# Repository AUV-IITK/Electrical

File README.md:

# Hyperion-Electrical

The repo contains all the schematics, PCB designs, simulations and other files related to Electrical subsystem of AUV-IITK including both past and current projects. A short description of every subdirectory is provided below in the reverse chronological order.

## actuator_board_v1.0 
The team is set to design and fabricate a single PCB for all the drivers that are needed for the actuators in the vehicle. The board also contains a slightly modified version and custom layout of Arduino Mega 2560's [reference design](https://www.arduino.cc/en/uploads/Main/arduino-mega2560-schematic.pdf?). Other than that, the following components form the crux of the board:

[MC34932](https://www.nxp.com/docs/en/data-sheet/MC34932.pdf) Dual H-Bridge Motor Driver to drive [BTD150 Thrusters](http://ocean-innovations.net/OceanInnovationsNEW/SeaBotix/BTD150_Data_Sheet.pdf) from SeaBotix

[Basic ESC R3](http://docs.bluerobotics.com/bescr3/) ESC from BlueRobotics to drive [T200 Thrusters](https://www.bluerobotics.com/store/thrusters/t200-thruster/) also from BlueRobotics

[DRV102](http://www.ti.com/product/DRV102) PWM Solenoid driver from Texas Instruments to control solenoid operated valves

## actuator_board_v0.1
This board is a prototype board intended to test the [MC34932](https://www.nxp.com/docs/en/data-sheet/MC34932.pdf) motor drivers and [Atmega2560](http://ww1.microchip.com/downloads/en/DeviceDoc/Atmel-2549-8-bit-AVR-Microcontroller-ATmega640-1280-1281-2560-2561_datasheet.pdf) circuit independently and observe their individual behavior before integrating them into v1.0 board. The board was fabricated and tested and it worked successfully. The team is moved onto designing the v1.0 board.

## BMSv2
This board is a concept-design of a Battery Management System to control, monitor and protect the Lithium Polymer batteries used in the vehicle. This board has not been fabricated due to technical difficulties we faced while testing the ICs. The following components are used in the board:

[Atxmega128A1U](http://ww1.microchip.com/downloads/en/DeviceDoc/Atmel-8385-8-and-16-bit-AVR-Microcontroller-ATxmega64A1U-ATxmega128A1U_datasheet.pdf) microcontroller as the brain of the board

[BQ76930](http://www.ti.com/lit/ds/symlink/bq76920.pdf) and [BQ78350-R1](https://www.ti.com/lit/ds/symlink/bq78350-r1.pdf?HQS=TI-null-null-sf-df-ds-null-wwe) battery management ICs from Texas Instruments

[TPS54531](http://www.ti.com/lit/ds/symlink/tps54531.pdf) Step Down DC-DC converters to create two voltage rails at 3.3V (to power the Atxmega chip) and 15V (To power an [Intel NUC](https://www.intel.in/content/www/in/en/products/boards-kits/nuc/kits/nuc5i7ryh.html) which is the main on-board computer in the vehicle). The board also provides an unregulated rail to power the [BTD150 Thrusters](http://ocean-innovations.net/OceanInnovationsNEW/SeaBotix/BTD150_Data_Sheet.pdf)

[ACS725](https://www.allegromicro.com/en/Products/Current-Sensor-ICs/Zero-To-Fifty-Amp-Integrated-Conductor-Sensor-ICs/ACS725.aspx) Current Sensors to monitor the current in each of the three rails

## BMS
This is a rudimentary battery management board that was created to act as a back-plane to connect multiple third-party modules. The board has been fabricated and tested and it worked succesfully. The board, however, didn't make it into the vehicle due to its large size.

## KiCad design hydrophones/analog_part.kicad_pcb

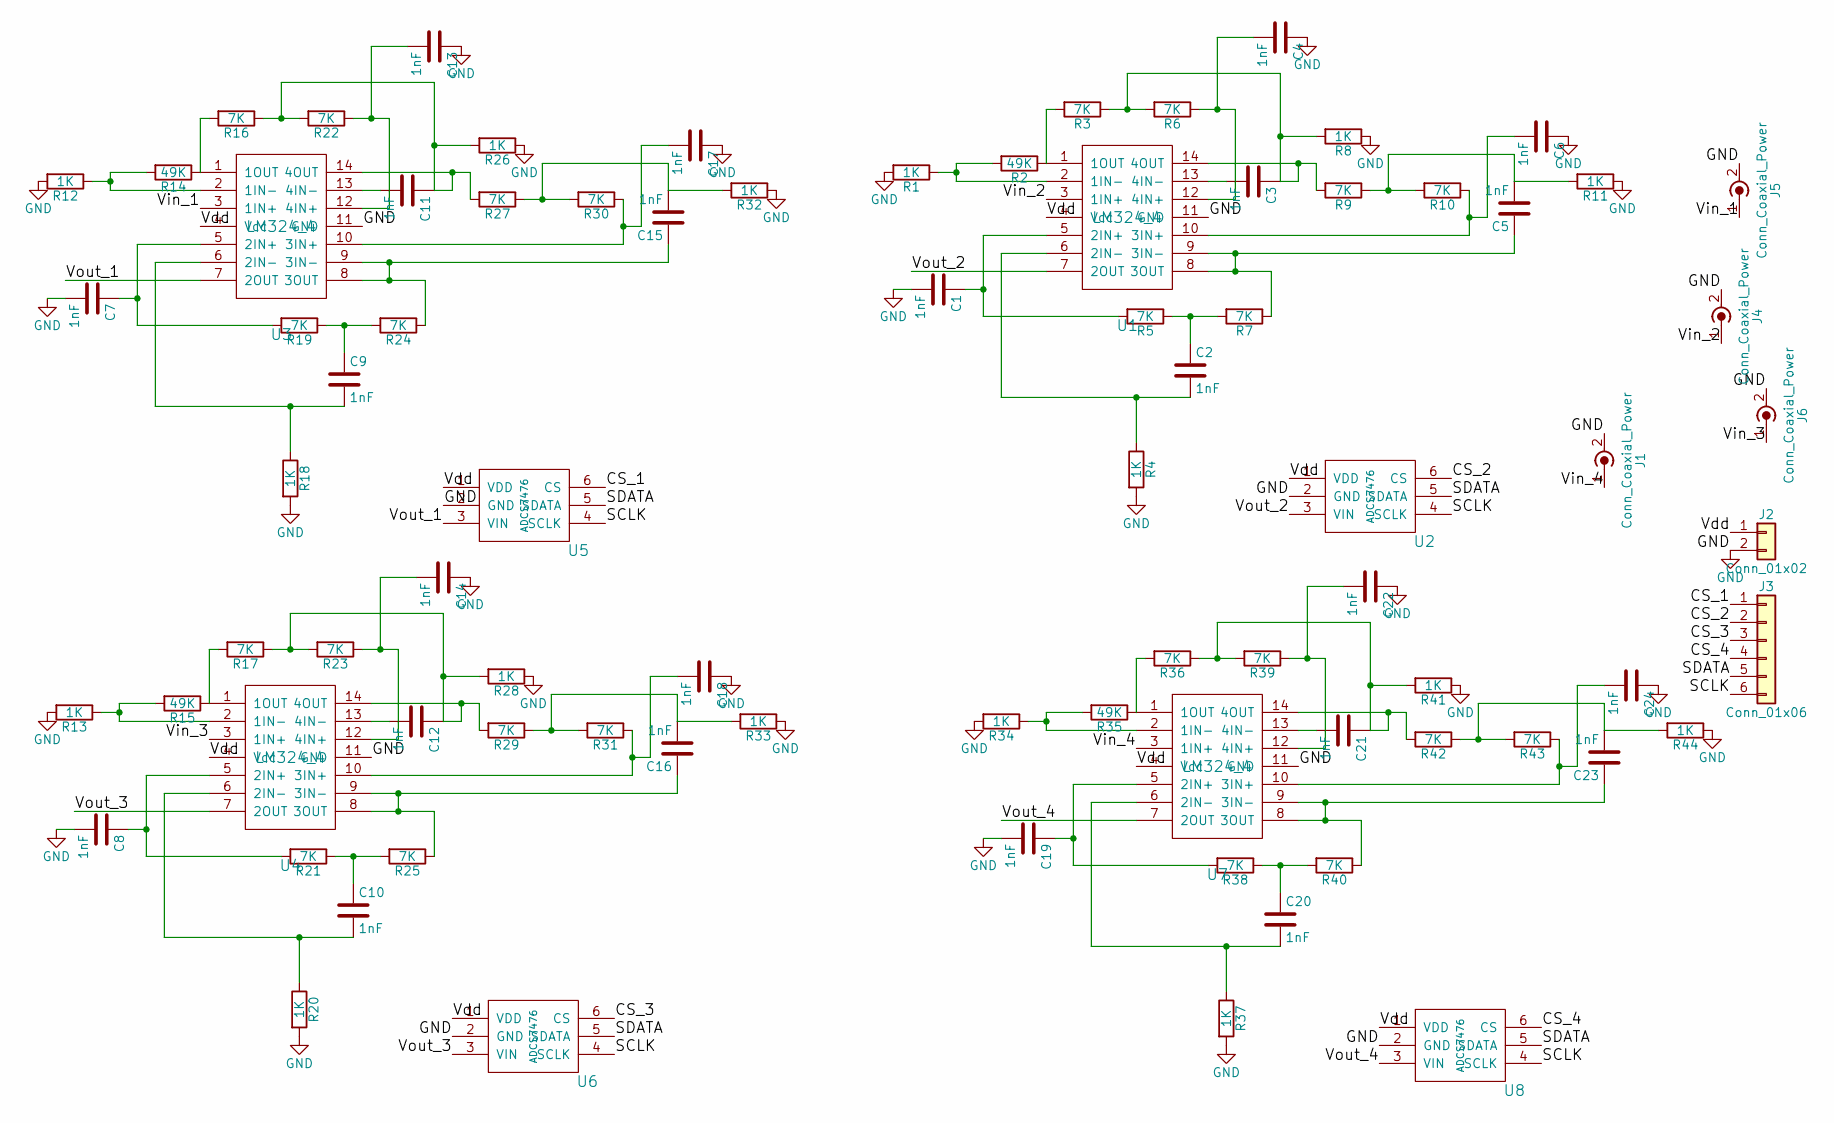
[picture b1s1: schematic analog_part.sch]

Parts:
C1, C2, C3, C4, C5, C6, C7, C8, C9, C10, C11, C12, C13, C14, C15, C16, C17, C18, C19, C20, C21, C22, C23, C24: 1nF; C_1206_HandSoldering
J1, J4, J5, J6: Conn_Coaxial_Power; bnc-ci
J2: Conn_01x02; Pin_Header_Angled_1x02_Pitch2.54mm
J3: Conn_01x06; Pin_Header_Angled_1x06_Pitch2.54mm
R1, R4, R8, R11, R12, R13, R18, R20, R26, R28, R32, R33, R34, R37, R41, R44: 1K; R_1206_HandSoldering
R2, R14, R15, R35: 49K; R_1206_HandSoldering
R3, R5, R6, R7, R9, R10, R16, R17, R19, R21, R22, R23, R24, R25, R27, R29, R30, R31, R36, R38, R39, R40, R42, R43: 7K; R_1206_HandSoldering
U1, U3, U4, U7: LM324_4; TSSOP-14_4.4x5mm_Pitch0.65mm
U2, U5, U6, U8: ADCS7476; SOT-23-6_Handsoldering

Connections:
/CS_1: J3.1, U5.6 (CS)
/CS_2: J3.2, U2.6 (CS)
/CS_3: J3.3, U6.6 (CS)
/CS_4: J3.4, U8.6 (CS)
/SCLK: J3.6, U2.4 (SCLK), U5.4 (SCLK), U6.4 (SCLK), U8.4 (SCLK)
/SDATA: J3.5, U2.5 (SDATA), U5.5 (SDATA), U6.5 (SDATA), U8.5 (SDATA)
/Vdd: J2.1, U1.4 (Vcc), U2.1 (VDD), U3.4 (Vcc), U4.4 (Vcc), U5.1 (VDD), U6.1 (VDD), U7.4 (Vcc), U8.1 (VDD)
/Vin_1: J5.1 (In), U3.3 (1IN+)
/Vin_2: J4.1 (In), U1.3 (1IN+)
/Vin_3: J6.1 (In), U4.3 (1IN+)
/Vin_4: J1.1 (In), U7.3 (1IN+)
/Vout_1: U3.7 (2OUT), U5.3 (VIN)
/Vout_2: U1.7 (2OUT), U2.3 (VIN)
/Vout_3: U4.7 (2OUT), U6.3 (VIN)
/Vout_4: U7.7 (2OUT), U8.3 (VIN)
GND: C1.2, C4.1, C6.1, C7.2, C8.2, C13.1, C14.1, C17.1, C18.1, C19.2, C22.1, C24.1, J1.2 (Ext), J2.2, J4.2 (Ext), J5.2 (Ext), J6.2 (Ext), R1.2, R4.2, R8.1, R11.1, R12.2, R13.2, R18.2, R20.2, R26.1, R28.1, R32.1, R33.1, R34.2, R37.2, R41.1, R44.1, U1.11 (GND), U2.2 (GND), U3.11 (GND), U4.11 (GND), U5.2 (GND), U6.2 (GND), U7.11 (GND), U8.2 (GND)
unnamed: C1.1, R5.2, U1.5 (2IN+)
unnamed: C2.1, R5.1, R7.2
unnamed: C2.2, R4.1, U1.6 (2IN-)
unnamed: C3.1, R3.1, R6.2, R8.2, R9.2, U1.14 (4OUT)
unnamed: C3.2, U1.13 (4IN-)
unnamed: C4.2, R6.1, U1.12 (4IN+)
unnamed: C5.1, R7.1, U1.8 (3OUT), U1.9 (3IN-)
unnamed: C5.2, R9.1, R10.2, R11.2
unnamed: C6.2, R10.1, U1.10 (3IN+)
unnamed: C7.1, R19.2, U3.5 (2IN+)
unnamed: C8.1, R21.2, U4.5 (2IN+)
unnamed: C9.1, R19.1, R24.2
unnamed: C9.2, R18.1, U3.6 (2IN-)
unnamed: C10.1, R21.1, R25.2
unnamed: C10.2, R20.1, U4.6 (2IN-)
unnamed: C11.1, R16.1, R22.2, R26.2, R27.2, U3.14 (4OUT)
unnamed: C11.2, U3.13 (4IN-)
unnamed: C12.1, R17.1, R23.2, R28.2, R29.2, U4.14 (4OUT)
unnamed: C12.2, U4.13 (4IN-)
unnamed: C13.2, R22.1, U3.12 (4IN+)
unnamed: C14.2, R23.1, U4.12 (4IN+)
unnamed: C15.1, R24.1, U3.8 (3OUT), U3.9 (3IN-)
unnamed: C15.2, R27.1, R30.2, R32.2
unnamed: C16.1, R25.1, U4.8 (3OUT), U4.9 (3IN-)
unnamed: C16.2, R29.1, R31.2, R33.2
unnamed: C17.2, R30.1, U3.10 (3IN+)
unnamed: C18.2, R31.1, U4.10 (3IN+)
unnamed: C19.1, R38.2, U7.5 (2IN+)
unnamed: C20.1, R38.1, R40.2
unnamed: C20.2, R37.1, U7.6 (2IN-)
unnamed: C21.1, R36.1, R39.2, R41.2, R42.2, U7.14 (4OUT)
unnamed: C21.2, U7.13 (4IN-)
unnamed: C22.2, R39.1, U7.12 (4IN+)
unnamed: C23.1, R40.1, U7.8 (3OUT), U7.9 (3IN-)
unnamed: C23.2, R42.1, R43.2, R44.2
unnamed: C24.2, R43.1, U7.10 (3IN+)
unnamed: R1.1, R2.2, U1.2 (1IN-)
unnamed: R2.1, R3.2, U1.1 (1OUT)
unnamed: R12.1, R14.2, U3.2 (1IN-)
unnamed: R13.1, R15.2, U4.2 (1IN-)
unnamed: R14.1, R16.2, U3.1 (1OUT)
unnamed: R15.1, R17.2, U4.1 (1OUT)
unnamed: R34.1, R35.2, U7.2 (1IN-)
unnamed: R35.1, R36.2, U7.1 (1OUT)

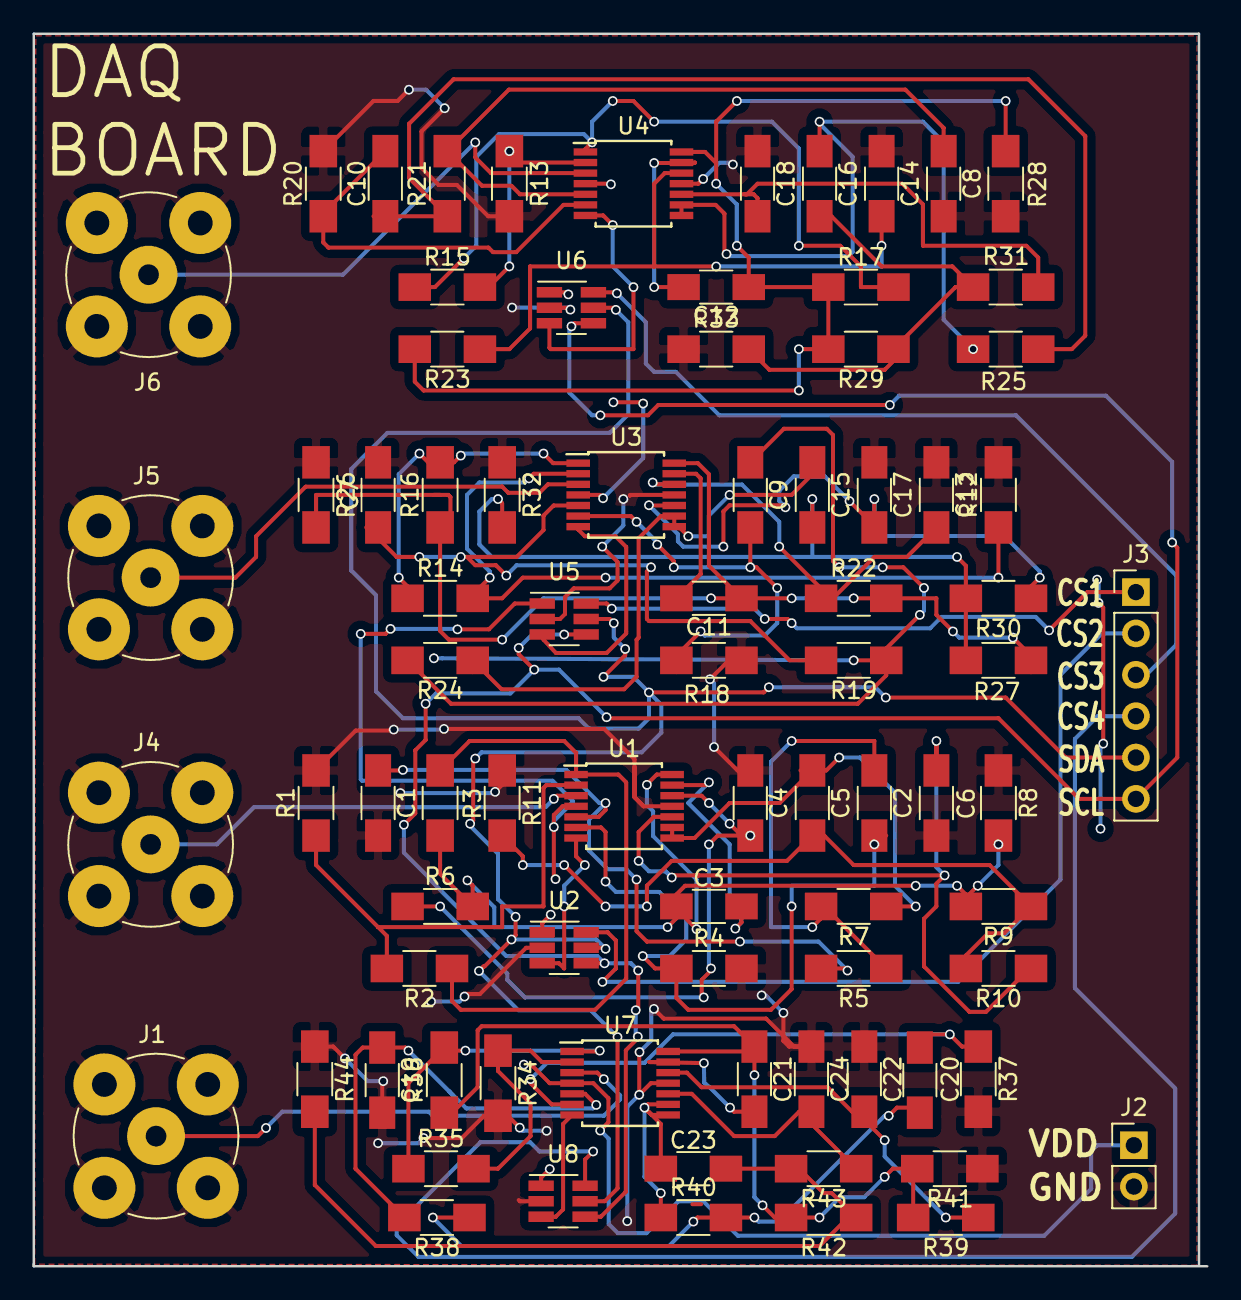
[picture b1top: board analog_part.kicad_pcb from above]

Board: 2 copper layers, 72.1 x 75.7 mm, 82 parts (0 on the bottom side), 60 nets.

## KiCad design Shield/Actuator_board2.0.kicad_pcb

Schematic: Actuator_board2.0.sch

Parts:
J1: Conn_01x05_Male; Pin_Header_Straight_1x05_Pitch2.54mm
J2, J3: Conn_01x13_Female; Socket_Strip_Straight_1x13_Pitch2.54mm
J4, J5, J8, J9, J12: Conn_01x04_Male; Pin_Header_Straight_1x04_Pitch2.54mm
J6: Conn_01x08_Male; Pin_Header_Straight_1x08_Pitch2.54mm
J7: Conn_01x07_Male; Pin_Header_Straight_1x07_Pitch2.54mm
J10, J11: Conn_01x02_Male; Pin_Header_Straight_1x02_Pitch2.54mm
XA1: Arduino_Mega2560_Shield

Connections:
/3.3V: J1.5, J11.1, J11.2, XA1.3V3 (3.3V)
/5V: J1.3, J4.1, J4.2, J4.3, J4.4, XA1.5V1 (5V)
/ANA1: J12.1, XA1.A4
/ANA2: J12.2, XA1.A5
/ANA3: J12.3, XA1.A6
/ANA4: J12.4, XA1.A7
/CS-1: J2.3, XA1.A0
/CS-2: J2.10, XA1.A1
/CS-3: J3.3, XA1.A2
/CS-4: J3.10, XA1.A3
/DIG1: J8.1, XA1.D40
/DIG2: J8.2, XA1.D41
/DIG3: J8.3, XA1.D42
/DIG4: J8.4, XA1.D43
/DIRA-1: J2.5, XA1.D22
/DIRA-2: J2.12, XA1.D24
/DIRA-3: J3.5, XA1.D26
/DIRA-4: J3.12, XA1.D28
/DIRB-1: J2.6, XA1.D23
/DIRB-2: J2.13, XA1.D25
/DIRB-3: J3.6, XA1.D27
/DIRB-4: J3.13, XA1.D29
/GND: J1.4, J2.1, J2.8, J3.1, J3.8, J5.1, J5.2, J5.3, J5.4, J6.2, J6.4, J6.6, J6.8, J7.7, XA1.GND1 (GND)
/PW1: J9.1, XA1.D6
/PW2: J9.2, XA1.D7
/PW3: J9.3, XA1.D8
/PW4: J9.4, XA1.D11
/PWM-1: J2.4, XA1.D2 (D2_INT0)
/PWM-2: J2.11, XA1.D3 (D3_INT1)
/PWM-3: J3.4, XA1.D4
/PWM-4: J3.11, XA1.D5
/S1: J7.1, XA1.D34
/S2: J7.2, XA1.D35
/S3: J7.3, XA1.D36
/S4: J7.4, XA1.D37
/S5: J7.5, XA1.D38
/S6: J7.6, XA1.D39
/SCL: J1.1, XA1.SCL
/SCL1: J10.2, XA1.D21 (D21_SCL)
/SDA: J1.2, XA1.SDA
/SDA1: J10.1, XA1.D20 (D20_SDA)
/T-5: J6.1, XA1.D30
/T-6: J6.3, XA1.D31
/T-7: J6.5, XA1.D32
/T-8: J6.7, XA1.D33

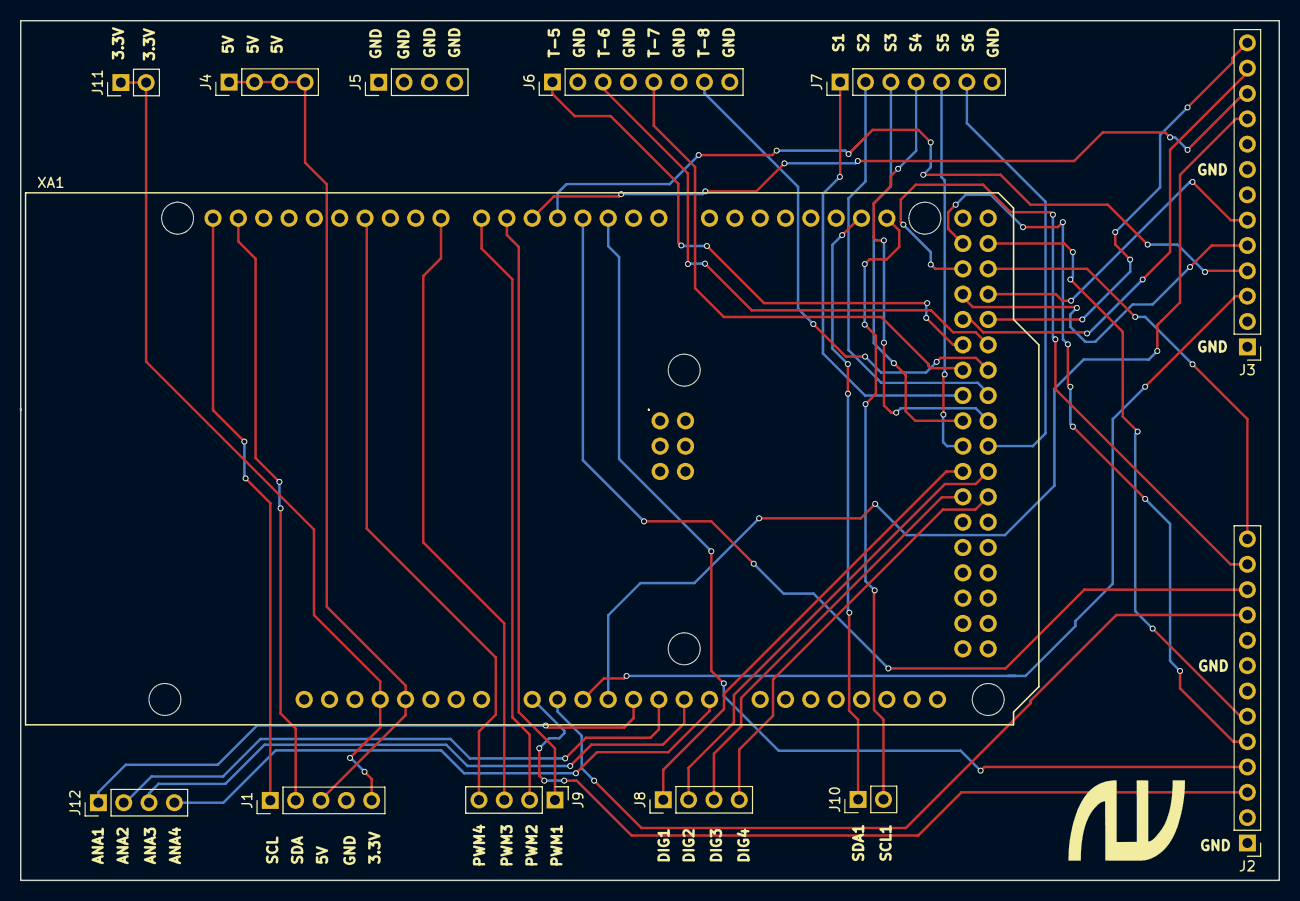
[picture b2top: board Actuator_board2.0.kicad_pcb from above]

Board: 2 copper layers, 126.2 x 86.2 mm, 13 parts (0 on the bottom side), 45 nets.

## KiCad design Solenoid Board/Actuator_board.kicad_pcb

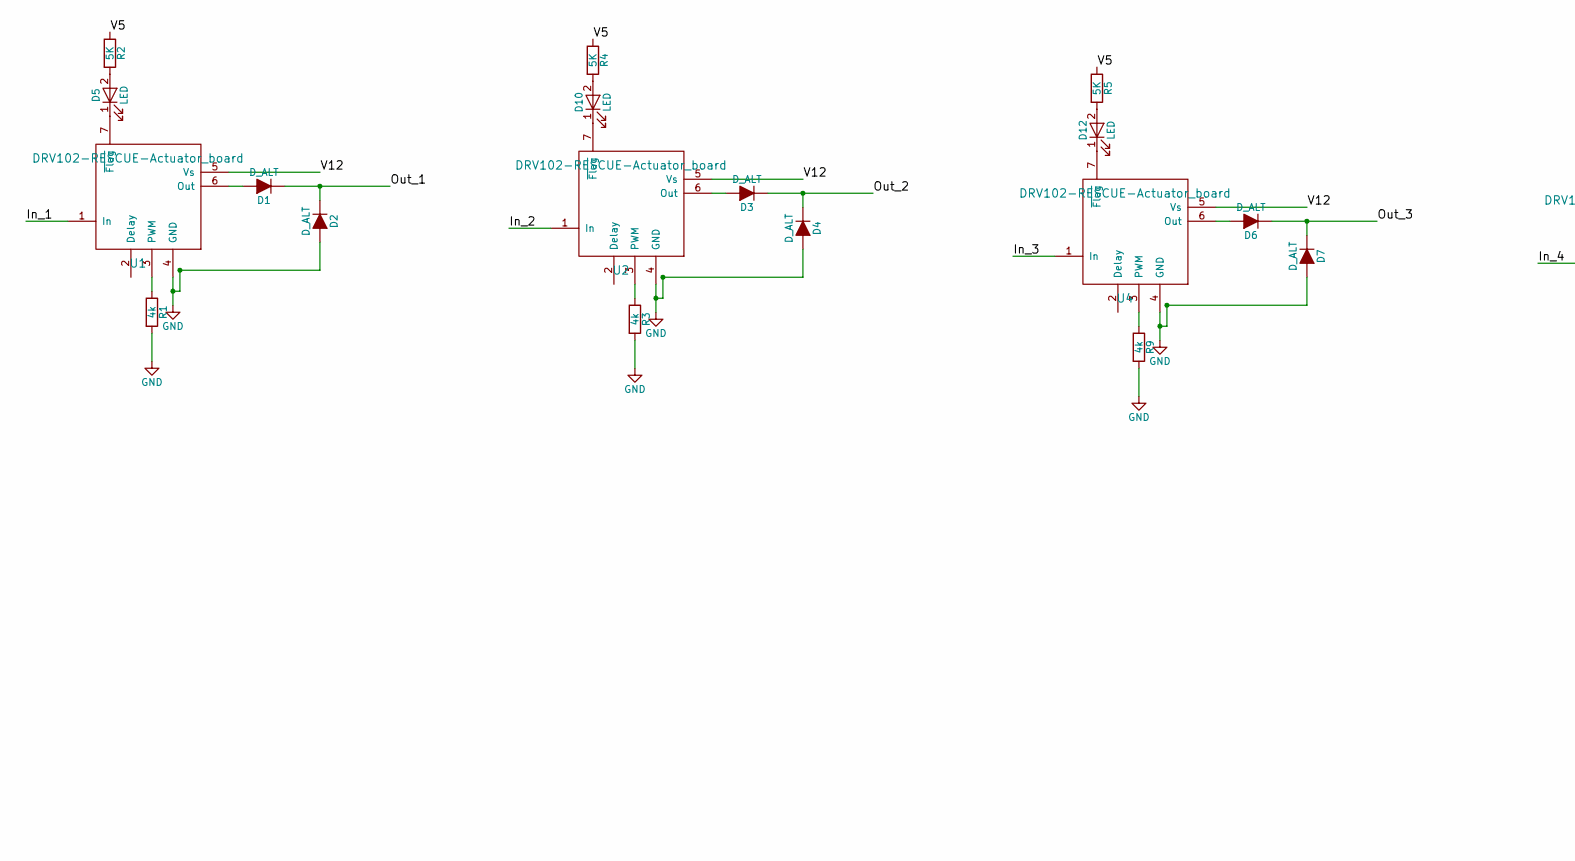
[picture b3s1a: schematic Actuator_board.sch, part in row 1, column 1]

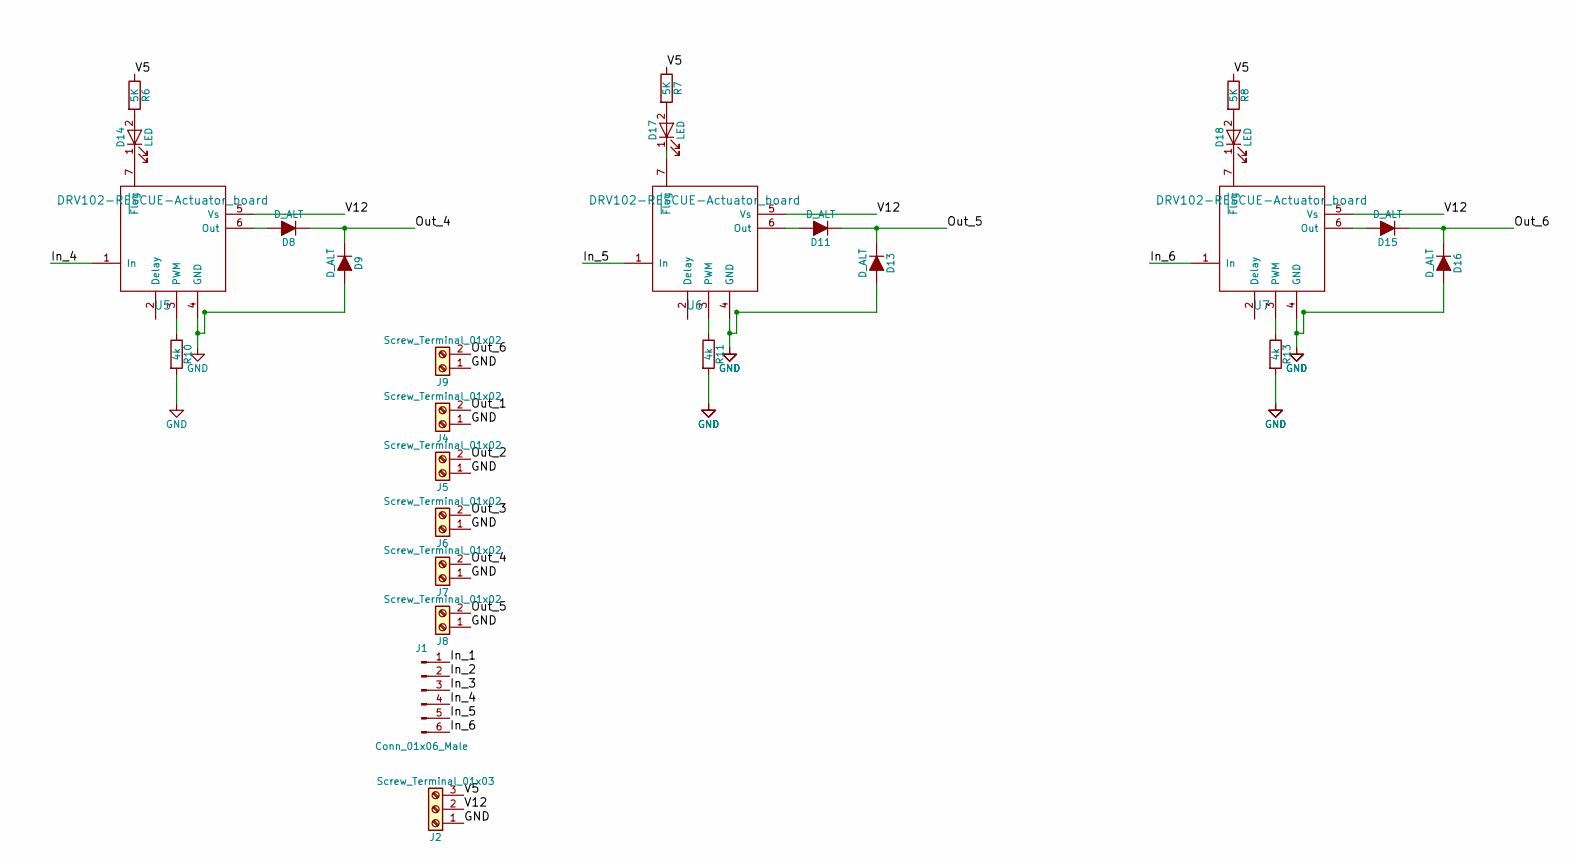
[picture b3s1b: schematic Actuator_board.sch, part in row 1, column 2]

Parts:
D1, D2, D3, D4, D6, D7, D8, D9, D11, D13, D15, D16: D_ALT; DO-214AB
D5: LED; LED_D2.0mm_W4.8mm_H2.5mm_FlatTop
D10, D12, D14, D17, D18: LED; LED_D3.0mm
J1: Conn_01x06_Male; Pin_Header_Straight_1x06_Pitch2.54mm
J2: Screw_Terminal_01x03; TerminalBlock_bornier-3_P5.08mm
J4, J5, J6, J7, J8, J9: Screw_Terminal_01x02; TerminalBlock_bornier-2_P5.08mm
R1, R3, R9, R10, R11, R13: 4k; R_1206
R2, R4, R5, R6, R7, R8: 5K; R_1206
U1, U2, U4, U5, U6, U7: DRV102-RESCUE-Actuator_board; TO-263-7_TabPin4

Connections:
/In_1: J1.1, U1.1 (In)
/In_2: J1.2, U2.1 (In)
/In_3: J1.3, U4.1 (In)
/In_4: J1.4, U5.1 (In)
/In_5: J1.5, U6.1 (In)
/In_6: J1.6, U7.1 (In)
/Out_1: D1.1 (K), D2.1 (K), J4.2
/Out_2: D3.1 (K), D4.1 (K), J5.2
/Out_3: D6.1 (K), D7.1 (K), J6.2
/Out_4: D8.1 (K), D9.1 (K), J7.2
/Out_5: D11.1 (K), D13.1 (K), J8.2
/Out_6: D15.1 (K), D16.1 (K), J9.2
/V5: J2.3, R2.1, R4.1, R5.1, R6.1, R7.1, R8.1
/V12: J2.2, U1.5 (Vs), U2.5 (Vs), U4.5 (Vs), U5.5 (Vs), U6.5 (Vs), U7.5 (Vs)
GND: D2.2 (A), D4.2 (A), D7.2 (A), D9.2 (A), D13.2 (A), D16.2 (A), J2.1, J4.1, J5.1, J6.1, J7.1, J8.1, J9.1, R1.2, R3.2, R9.2, R10.2, R11.2, R13.2, U1.4 (GND), U2.4 (GND), U4.4 (GND), U5.4 (GND), U6.4 (GND), U7.4 (GND)
unnamed: D1.2 (A), U1.6 (Out)
unnamed: D3.2 (A), U2.6 (Out)
unnamed: D5.1 (K), U1.7 (~Flag)
unnamed: D5.2 (A), R2.2
unnamed: D6.2 (A), U4.6 (Out)
unnamed: D8.2 (A), U5.6 (Out)
unnamed: D10.1 (K), U2.7 (~Flag)
unnamed: D10.2 (A), R4.2
unnamed: D11.2 (A), U6.6 (Out)
unnamed: D12.1 (K), U4.7 (~Flag)
unnamed: D12.2 (A), R5.2
unnamed: D14.1 (K), U5.7 (~Flag)
unnamed: D14.2 (A), R6.2
unnamed: D15.2 (A), U7.6 (Out)
unnamed: D17.1 (K), U6.7 (~Flag)
unnamed: D17.2 (A), R7.2
unnamed: D18.1 (K), U7.7 (~Flag)
unnamed: D18.2 (A), R8.2
unnamed: R1.1, U1.3 (PWM)
unnamed: R3.1, U2.3 (PWM)
unnamed: R9.1, U4.3 (PWM)
unnamed: R10.1, U5.3 (PWM)
unnamed: R11.1, U6.3 (PWM)
unnamed: R13.1, U7.3 (PWM)

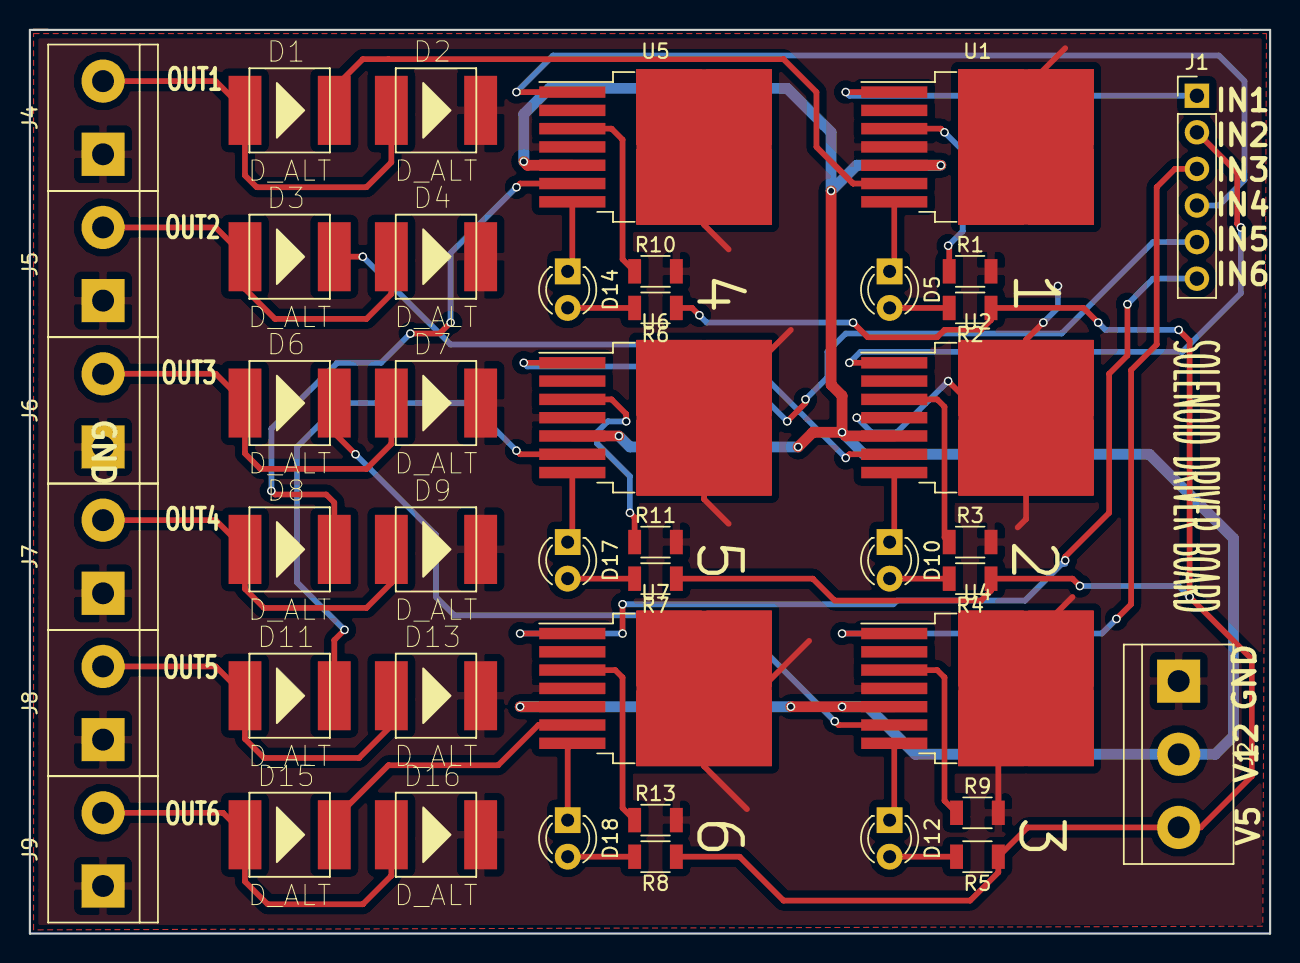
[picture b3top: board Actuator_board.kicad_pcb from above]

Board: 2 copper layers, 86.1 x 62.7 mm, 44 parts (0 on the bottom side), 39 nets.

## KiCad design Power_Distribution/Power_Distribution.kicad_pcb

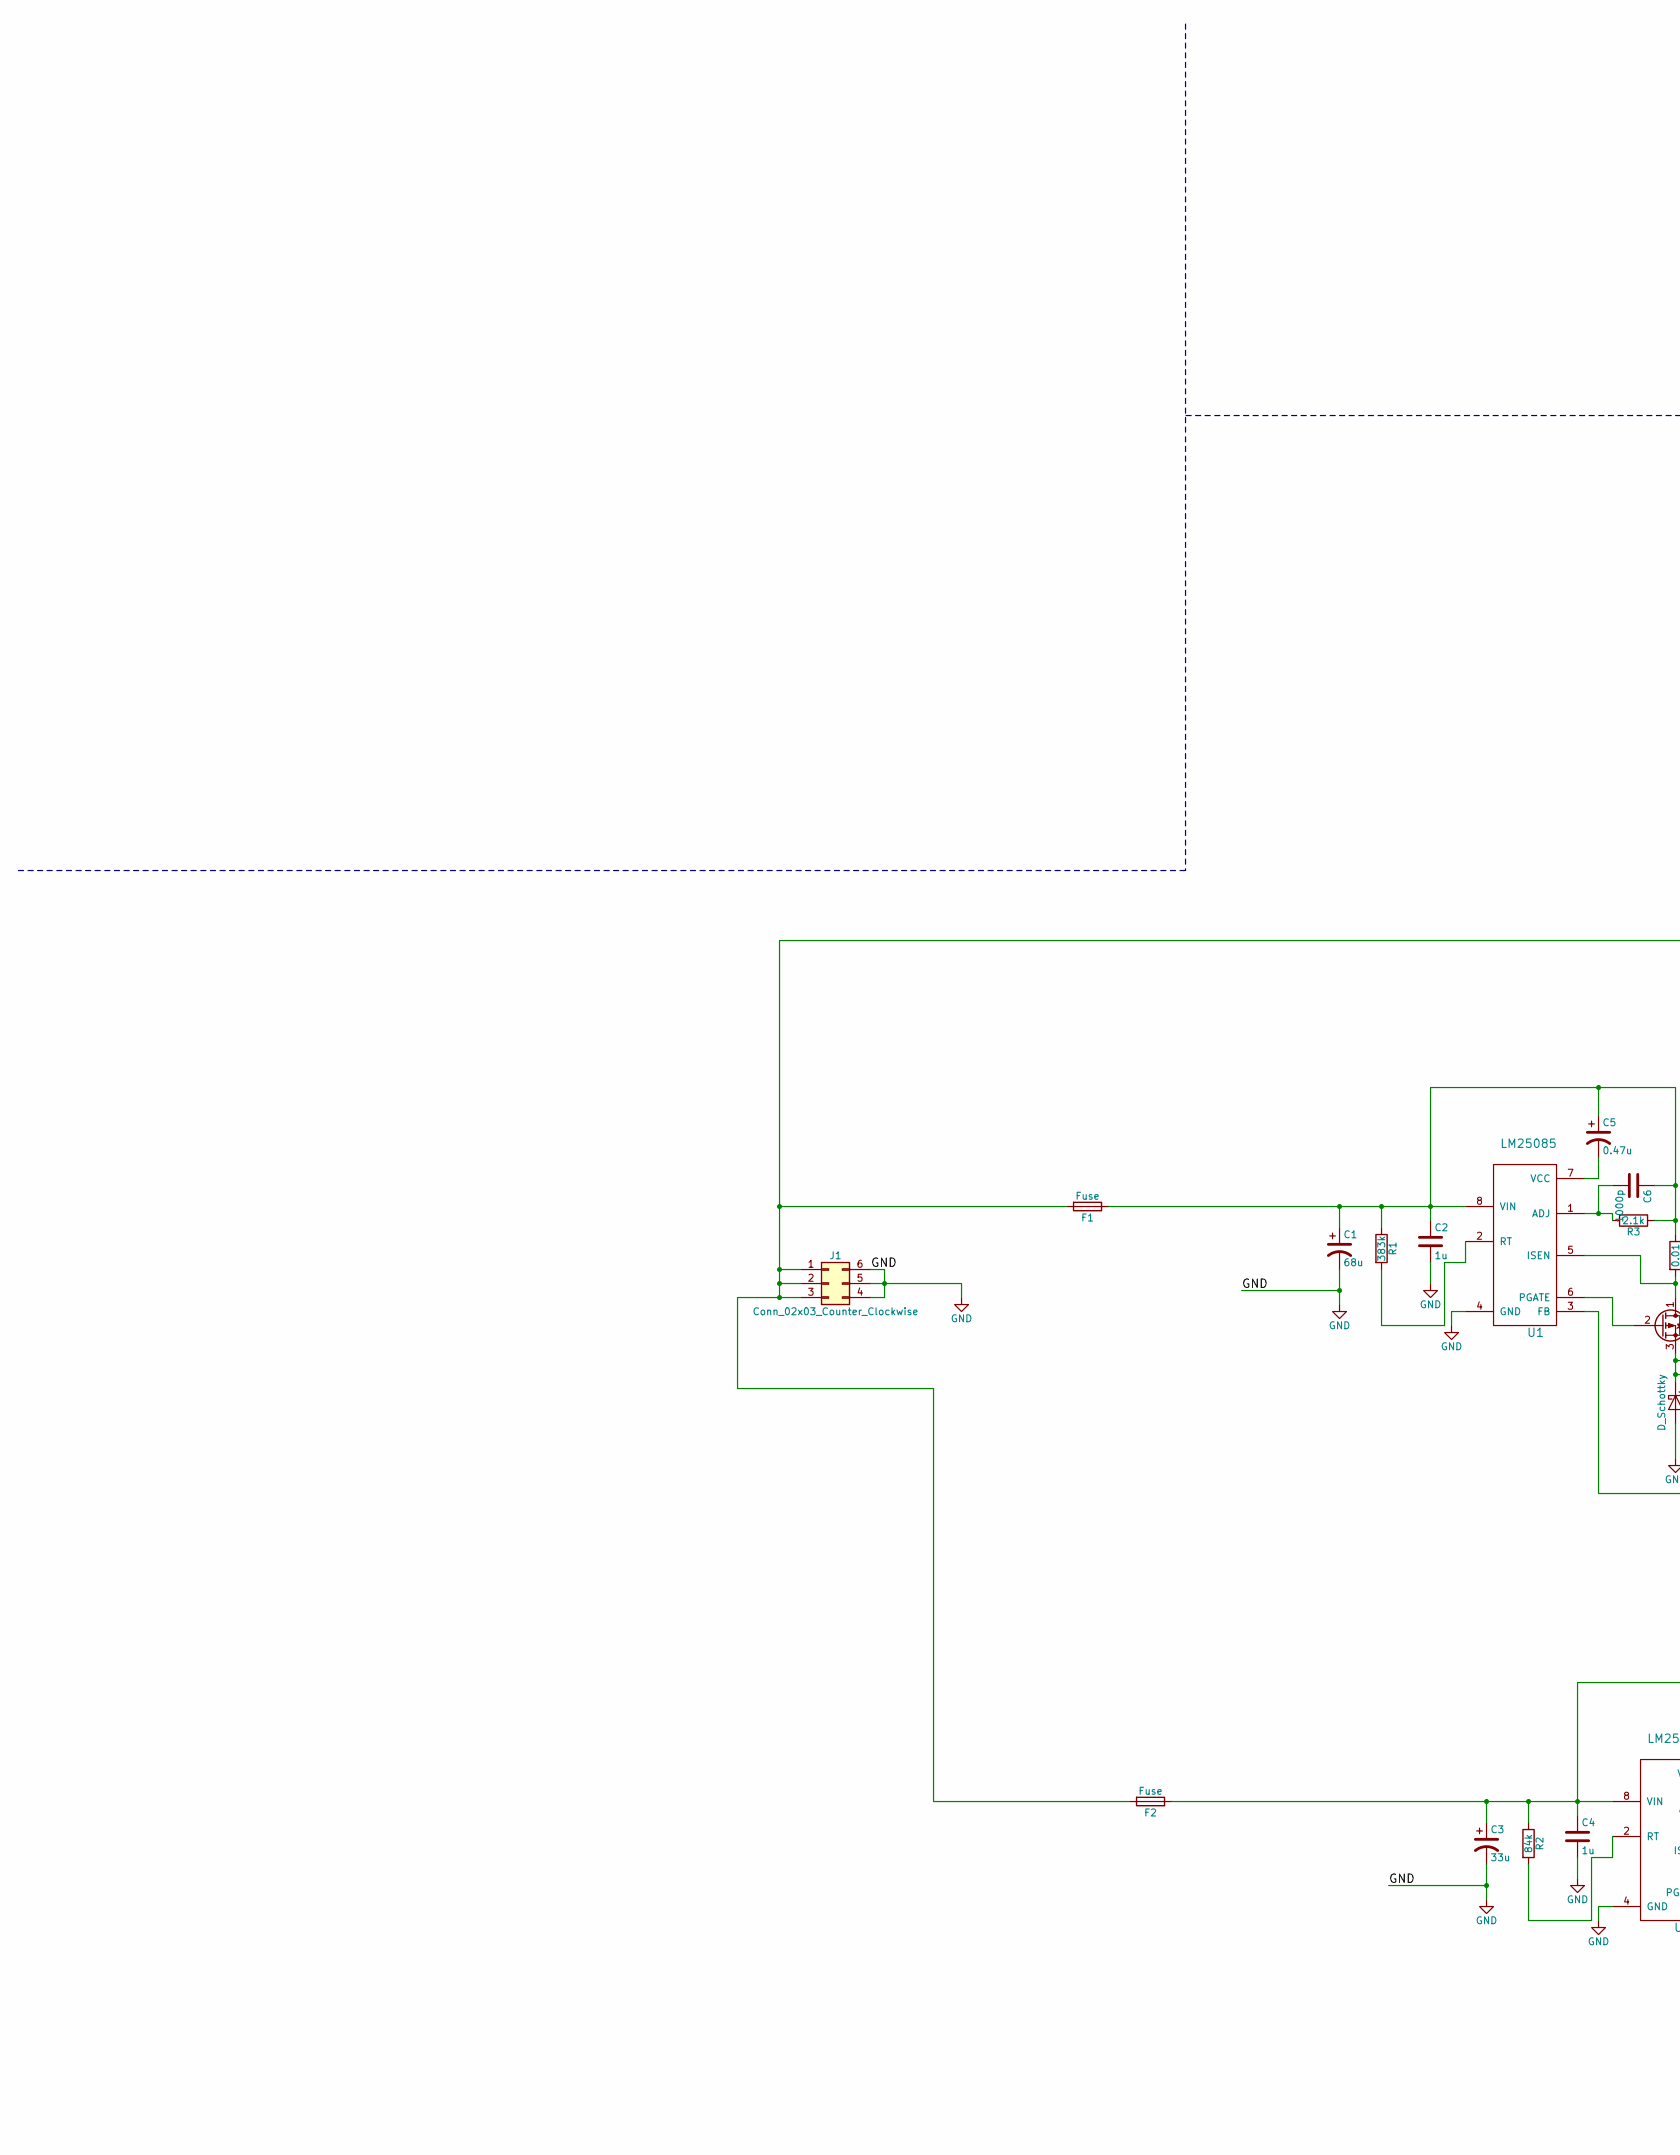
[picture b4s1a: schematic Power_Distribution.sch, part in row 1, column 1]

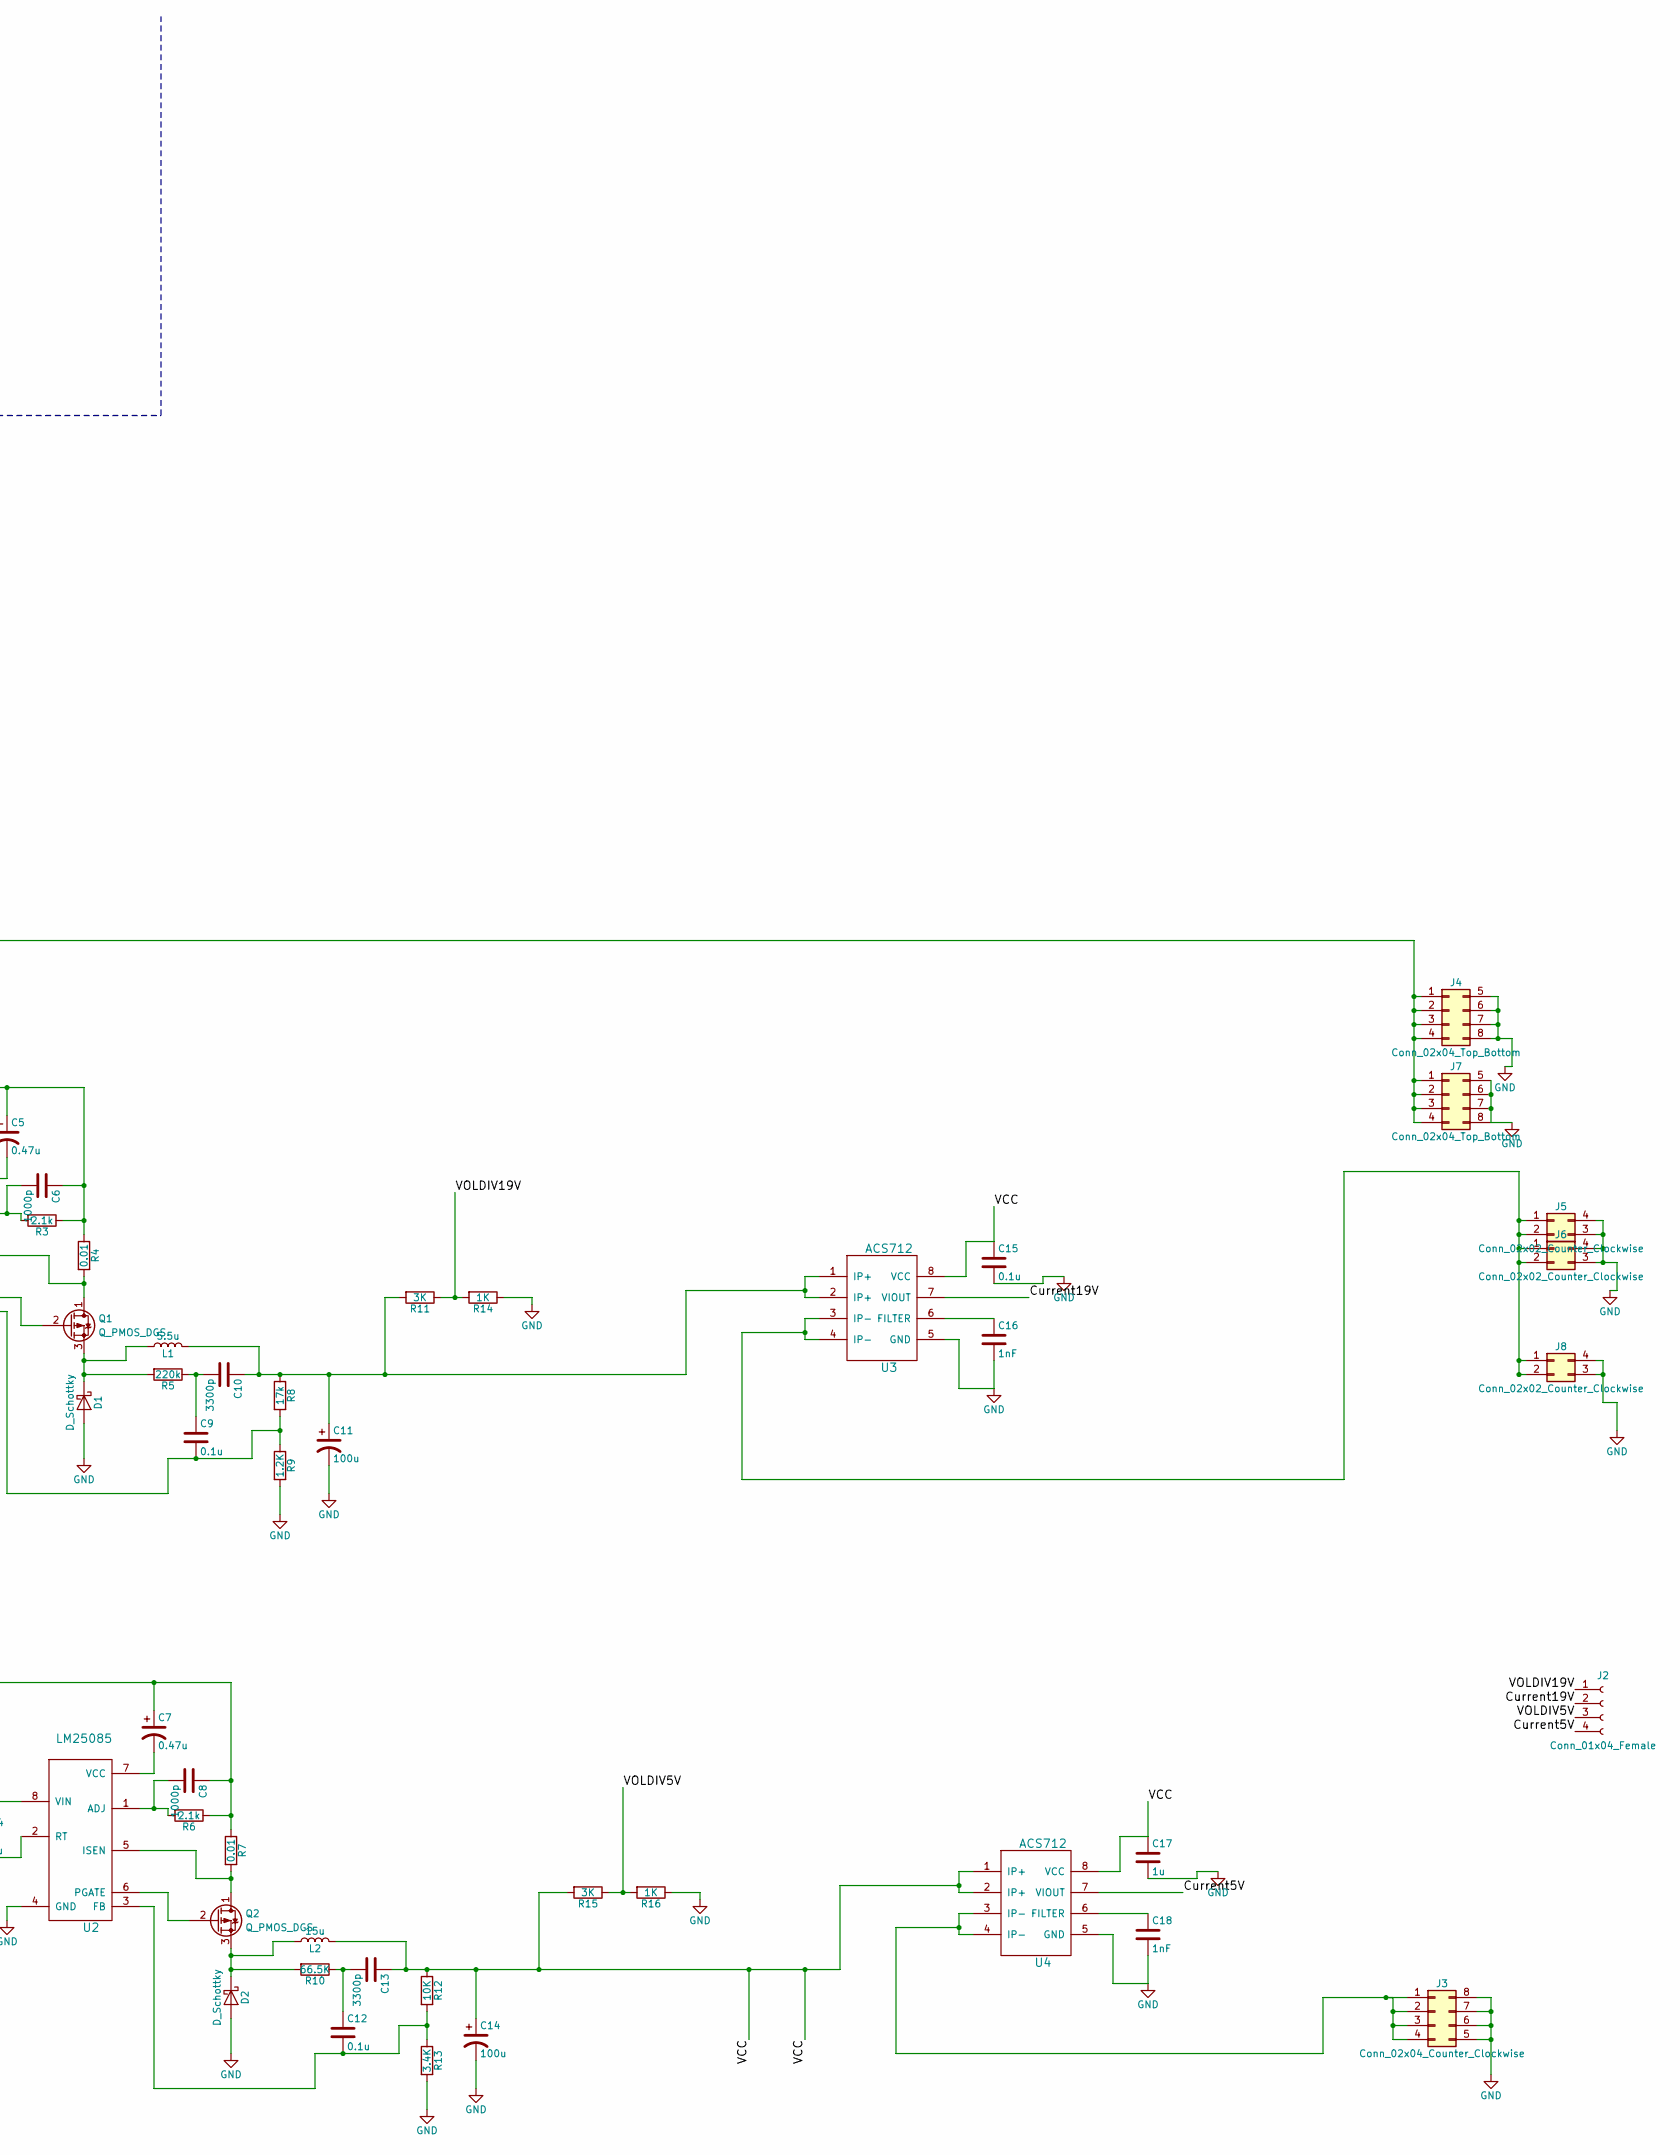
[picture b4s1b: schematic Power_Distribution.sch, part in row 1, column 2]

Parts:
C1: 68u; CP_Radial_D6.3mm_P2.50mm
C2, C4, C17: 1u; C_1206
C3: 33u; CP_Radial_D6.3mm_P2.50mm
C5, C7: 0.47u; CP_Radial_D5.0mm_P2.00mm
C6, C8: 1000p; C_1206
C9, C12, C15: 0.1u; C_1206
C10, C13: 3300p; C_1206
C11, C14: 100u; CP_Radial_D8.0mm_P3.50mm
C16, C18: 1nF; C_1206
D1, D2: D_Schottky; TO-220-2_Vertical
F1, F2: Fuse; Fuse_SMD1206_Wave
J1: Conn_02x03_Counter_Clockwise; Molex_MegaFit_2x03x5.70mm_Straight
J2: Conn_01x04_Female; Molex_PicoClasp_501331-0407_1x04_P1.0mm_Vertical
J3: Conn_02x04_Counter_Clockwise; Molex_MegaFit_2x04x5.70mm_Straight
J4, J7: Conn_02x04_Top_Bottom; Molex_MegaFit_2x04x5.70mm_Straight
J5, J6, J8: Conn_02x02_Counter_Clockwise; Molex_MegaFit_2x02x5.70mm_Straight
L1: 5.5u; L_10.4x10.4_H4.8
L2: 15u; inductor_13.5x12.5
Q1, Q2: Q_PMOS_DGS; TO-252-3_TabPin2
R1: 383k; R_1206
R2: 84k; R_1206
R3, R6: 2.1k; R_1206
R4, R7: 0.01; R_1206
R5: 220k; R_1206
R8: 17k; R_1206
R9: 1.2K; R_1206
R10: 66.5K; R_1206
R11, R15: 3K; R_1206
R12: 10K; R_1206
R13: 3.4K; R_1206
R14, R16: 1K; R_1206
U1, U2: LM25085; VSSOP-8_3.0x3.0mm_Pitch0.65mm
U3, U4: ACS712; SOIC-8_3.9x4.9mm_Pitch1.27mm

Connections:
/Current5V: J2.4, U4.7 (VIOUT)
/Current19V: J2.2, U3.7 (VIOUT)
/VCC: C13.1, C14.1, C15.1, C17.1, L2.2, R12.1, R15.2, U3.8 (VCC), U4.1 (IP+), U4.2 (IP+), U4.8 (VCC)
/VOLDIV5V: J2.3, R15.1, R16.2
/VOLDIV19V: J2.1, R11.1, R14.2
GND: C1.2, C2.2, C3.2, C4.2, C11.2, C14.2, C15.2, C16.2, C17.2, C18.2, D1.2 (A), D2.2 (A), J1.4, J1.5, J1.6, J3.5, J3.6, J3.7, J3.8, J4.5, J4.6, J4.7, J4.8, J5.3, J5.4, J6.3, J6.4, J7.5, J7.6, J7.7, J7.8, J8.3, J8.4, R9.2, R13.2, R14.1, R16.1, U1.4 (GND), U2.4 (GND), U3.5 (GND), U4.5 (GND)
unnamed: C1.1, C2.1, C5.1, C6.1, F1.1, R1.1, R3.1, R4.1, U1.8 (VIN)
unnamed: C3.1, C4.1, C7.1, C8.1, F2.1, R2.1, R6.1, R7.1, U2.8 (VIN)
unnamed: C5.2, U1.7 (VCC)
unnamed: C6.2, R3.2, U1.1 (ADJ)
unnamed: C7.2, U2.7 (VCC)
unnamed: C8.2, R6.2, U2.1 (ADJ)
unnamed: C9.2, R8.2, R9.1, U1.3 (FB)
unnamed: C10.1, C11.1, L1.2, R8.1, R11.2, U3.1 (IP+), U3.2 (IP+)
unnamed: C9.1, C10.2, R5.1
unnamed: C12.1, C13.2, R10.1
unnamed: C12.2, R12.2, R13.1, U2.3 (FB)
unnamed: C16.1, U3.6 (FILTER)
unnamed: C18.1, U4.6 (FILTER)
unnamed: D1.1 (K), L1.1, Q1.3 (S), R5.2
unnamed: D2.1 (K), L2.1, Q2.3 (S), R10.2
unnamed: F1.2, F2.2, J1.1, J1.2, J1.3, J4.1, J4.2, J4.3, J4.4, J7.1, J7.2, J7.3, J7.4
unnamed: J3.1, J3.2, J3.3, J3.4, U4.3 (IP-), U4.4 (IP-)
unnamed: J5.1, J5.2, J6.1, J6.2, J8.1, J8.2, U3.3 (IP-), U3.4 (IP-)
unnamed: Q1.1 (D), R4.2, U1.5 (ISEN)
unnamed: Q1.2 (G), U1.6 (PGATE)
unnamed: Q2.1 (D), R7.2, U2.5 (ISEN)
unnamed: Q2.2 (G), U2.6 (PGATE)
unnamed: R1.2, U1.2 (RT)
unnamed: R2.2, U2.2 (RT)
